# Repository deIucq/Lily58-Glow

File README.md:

# Lily58 - χ
ビルドガイドは[こちら](https://github.com/deIucq/Lily58-X/blob/master/buildguide.md)

BuildGuide is [here](https://github.com/deIucq/Lily58-X/blob/master/buildguide.md)

Lily58-χ(カイ)はLily58からforkされた[Lily58-glow](https://github.com/qtkb/Lily58-Glow)に以下の変更を加えたものです。
検索性向上のために，ここ以外ではLily58-Xと表記します。

- RGBLEDのpad配置をSK6812mini-e用に変更
- Underglow用LEDの場所・数を変更
- BLE Micro Proのインジケータ用にLEDを追加
- トラックパッド用のピンヘッダ・ネジ穴を追加
- 縁を覆うようなケースを追加
- I2Cと単線シリアルをスイッチできるようにジャンパーを追加
- TRRSジャックのピンアサインを変更(moduloと同様のピンアサイン)

Lily58-χ(chi) is a forked version of [Lily58-glow](https://github.com/qtkb/Lily58-Glow) from Lily58 with the following changes.

- Change RGB LED pad to SK6812mini-e's one.
- Change place and number of LEDs for underglow.
- Add LED for BLE Micro Pro's indicator.
- Add new Pinheader for trackpad modules.
- Add case that can cover edge.
- Add jumber for switching I2C and Serial
- Change TRRS pin assign

このプロジェクトは開発中です。PCBの設計にミスがある可能性があります。
This project is still in progress. There may be some mistakes in PCB design.

# Parts

| Part Name                                                    | Quantity |
| ------------------------------------------------------------ | -------- |
| PCB                                                          | 2        |
| Top Case,Mid Case,Bottom Case(t2 acrylic)                    | 2        |
| Pro Micro or BLE Micro Pro                                   | 2        |
| Choc Key Switch                                              | 58       |
| Keycap                                                       | 58       |
| SK6812-MINI-E                                                | 58       |
| OLED                                                         | 2        |
| Diode 1N4148W                                                | 58       |
| Tact switch                                                  | 2        |
| TRRS jack (option for Pro Micro)                             | 2        |
| TRRS cable (opton for Pro Micro)                             | 1        |
| M2 screw 10mm                                                | 10       |
| M2 Nut                                                       | 20       |
| M2 spacer 10mm                                               | 4        |
| M2 screw 4mm                                                 | 8        |
| Urethane cushion                                             | 10       |
| Low profile pin header(1×4 & 1×6)                            | 2        |
| [option] RKJXY1000006 trackpad with DIP convertPCB           | 1        |
| [option] 1608 LED                                            | 1        |
| [option] Constant current diode or resistor                  | 1        |

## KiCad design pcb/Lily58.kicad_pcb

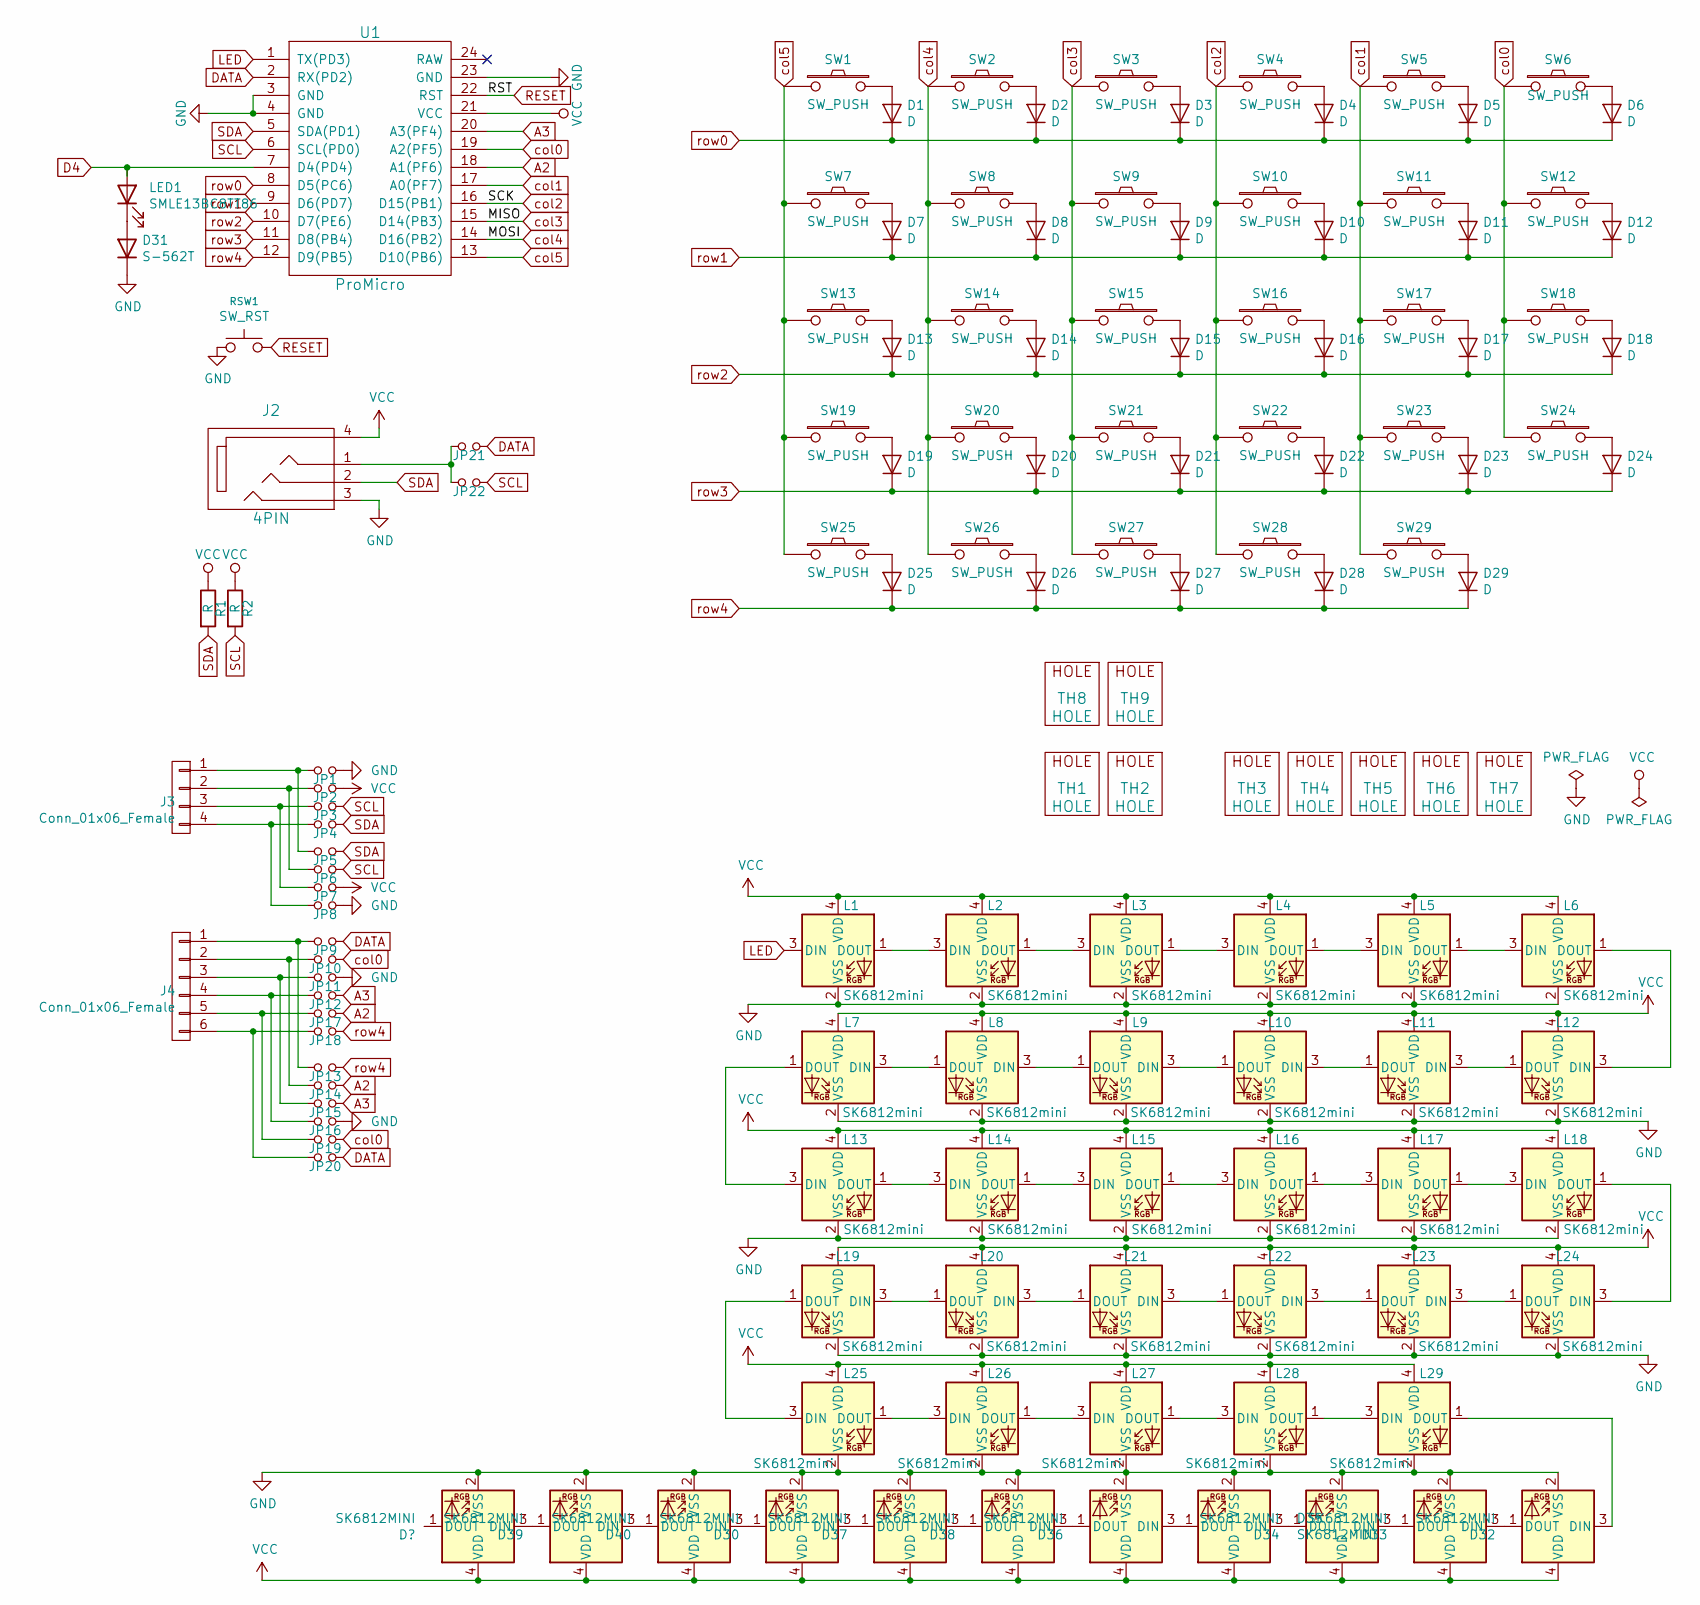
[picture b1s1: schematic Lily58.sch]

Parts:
D1, D2, D3, D4, D5, D6, D7, D8, D9, D10, D11, D12, D13, D14, D15, D16, D17, D18, D19, D20, D21, D22, D23, D24, D25, D26, D27, D28, D29: D; Diode_SOD123
D30, D32, D33, D34, D35, D36, D37, D38, D39, D40: SK6812MINI; SK6812MINI_underglow_rev
D31: S-562T; D_1206_3216Metric_Pad1.42x1.75mm_HandSolder
J2: 4PIN; MJ-4PP-9
J3: Conn_01x06_Female; OLED_4Pin
J4: Conn_01x06_Female; OLED_6Pin
JP1, JP2, JP3, JP4, JP5, JP6, JP7, JP8, JP9, JP10, JP11, JP12, JP13, JP14, JP15, JP16, JP17, JP18, JP19, JP20: Jumper_NO_Small; Jumper
JP21: 1S; Jumper
JP22: I2C; Jumper
L1, L2, L3, L4, L5, L6, L7, L8, L9, L10, L11, L12, L13, L14, L15, L16, L17, L18, L19, L20, L21, L22, L23, L24, L25, L26, L27, L28, L29: SK6812mini; SK6812MINI_rev
LED1: SMLE13BC8TT86; LED_0603_1608Metric_Pad1.05x0.95mm_HandSolder
R1, R2: R; RESISTOR_mini
RSW1: SW_RST; TACT_SWITCH_TVBP06
SW1, SW2, SW3, SW4, SW5, SW6, SW7, SW8, SW9, SW10, SW11, SW12, SW13, SW14, SW15, SW16, SW17, SW18, SW19, SW20, SW21, SW22, SW23, SW24, SW25, SW27, SW28, SW29: SW_PUSH; MX_PG1350_FLIP_HOLES_18mm
SW26: SW_PUSH; MX_PG1350_FLIP_HOLES_27mm
TH1, TH2, TH8, TH9: HOLE; HOLE_M2
TH3, TH4, TH5, TH6, TH7: HOLE; HOLE_M2_TH
U1: ProMicro; ProMicro_rev2

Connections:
A2: JP14.2, JP17.2, U1.18 (A1(PF6))
A3: JP12.2, JP15.2, U1.20 (A3(PF4))
D4: LED1.2 (A), U1.7 (D4(PD4))
DATA: JP9.2, JP20.2, JP21.2, U1.2 (RX(PD2))
GND: D30.2 (VSS), D31.1 (K), D32.2 (VSS), D33.2 (VSS), D34.2 (VSS), D35.2 (VSS), D36.2 (VSS), D37.2 (VSS), D38.2 (VSS), D39.2 (VSS), D40.2 (VSS), J2.3, JP1.2, JP8.2, JP11.2, JP16.2, L1.2 (VSS), L2.2 (VSS), L3.2 (VSS), L4.2 (VSS), L5.2 (VSS), L6.2 (VSS), L7.2 (VSS), L8.2 (VSS), L9.2 (VSS), L10.2 (VSS), L11.2 (VSS), L12.2 (VSS), L13.2 (VSS), L14.2 (VSS), L15.2 (VSS), L16.2 (VSS), L17.2 (VSS), L18.2 (VSS), L19.2 (VSS), L20.2 (VSS), L21.2 (VSS), L22.2 (VSS), L23.2 (VSS), L24.2 (VSS), L25.2 (VSS), L26.2 (VSS), L27.2 (VSS), L28.2 (VSS), L29.2 (VSS), RSW1.1, U1.3 (GND), U1.4 (GND), U1.23 (GND); also elsewhere on the board
LED: L1.3 (DIN), U1.1 (TX(PD3))
unnamed: D1.2 (A), SW1.2
unnamed: D2.2 (A), SW2.2
unnamed: D3.2 (A), SW3.2
unnamed: D4.2 (A), SW4.2
unnamed: D5.2 (A), SW5.2
unnamed: D6.2 (A), SW6.2
unnamed: D7.2 (A), SW7.2
unnamed: D8.2 (A), SW8.2
unnamed: D9.2 (A), SW9.2
unnamed: D10.2 (A), SW10.2
unnamed: D11.2 (A), SW11.2
unnamed: D12.2 (A), SW12.2
unnamed: D13.2 (A), SW13.2
unnamed: D14.2 (A), SW14.2
unnamed: D15.2 (A), SW15.2
unnamed: D16.2 (A), SW16.2
unnamed: D17.2 (A), SW17.2
unnamed: D18.2 (A), SW18.2
unnamed: D19.2 (A), SW19.2
unnamed: D20.2 (A), SW20.2
unnamed: D21.2 (A), SW21.2
unnamed: D22.2 (A), SW22.2
unnamed: D23.2 (A), SW23.2
unnamed: D24.2 (A), SW24.2
unnamed: D25.2 (A), SW25.2
unnamed: D26.2 (A), SW26.2
unnamed: D27.2 (A), SW27.2
unnamed: D28.2 (A), SW28.2
unnamed: D29.2 (A), SW29.2
unnamed: D30.1 (DOUT), D40.3 (DIN)
unnamed: D30.3 (DIN), D37.1 (DOUT)
unnamed: D31.2 (A), LED1.1 (K)
unnamed: D32.1 (DOUT), D33.3 (DIN)
unnamed: D32.3 (DIN), L29.1 (DOUT)
unnamed: D33.1 (DOUT), D34.3 (DIN)
unnamed: D34.1 (DOUT), D35.3 (DIN)
unnamed: D35.1 (DOUT), D36.3 (DIN)
unnamed: D36.1 (DOUT), D38.3 (DIN)
unnamed: D37.3 (DIN), D38.1 (DOUT)
unnamed 45: D39.1 (DOUT); also elsewhere on the board
unnamed: D39.3 (DIN), D40.1 (DOUT)
unnamed: J2.1, JP21.1, JP22.1
unnamed: J3.1, JP1.1, JP5.1
unnamed: J3.2, JP2.1, JP6.1
unnamed: J3.3, JP3.1, JP7.1
unnamed: J3.4, JP4.1, JP8.1
unnamed: J4.1, JP9.1, JP13.1
unnamed: J4.2, JP10.1, JP14.1
unnamed: J4.3, JP11.1, JP15.1
unnamed: J4.4, JP12.1, JP16.1
unnamed: J4.5, JP17.1, JP19.1
unnamed: J4.6, JP18.1, JP20.1
unnamed: L1.1 (DOUT), L2.3 (DIN)
unnamed: L2.1 (DOUT), L3.3 (DIN)
unnamed: L3.1 (DOUT), L4.3 (DIN)
unnamed: L4.1 (DOUT), L5.3 (DIN)
unnamed: L5.1 (DOUT), L6.3 (DIN)
unnamed: L7.3 (DIN), L8.1 (DOUT)
unnamed: L8.3 (DIN), L9.1 (DOUT)
unnamed: L9.3 (DIN), L10.1 (DOUT)
unnamed: L10.3 (DIN), L11.1 (DOUT)
unnamed: L11.3 (DIN), L12.1 (DOUT)
unnamed: L6.1 (DOUT), L12.3 (DIN)
unnamed: L13.1 (DOUT), L14.3 (DIN)
unnamed: L7.1 (DOUT), L13.3 (DIN)
unnamed: L14.1 (DOUT), L15.3 (DIN)
unnamed: L15.1 (DOUT), L16.3 (DIN)
unnamed: L16.1 (DOUT), L17.3 (DIN)
unnamed: L17.1 (DOUT), L18.3 (DIN)
unnamed: L18.1 (DOUT), L24.3 (DIN)
unnamed: L19.1 (DOUT), L25.3 (DIN)
unnamed: L19.3 (DIN), L20.1 (DOUT)
unnamed: L20.3 (DIN), L21.1 (DOUT)
unnamed: L21.3 (DIN), L22.1 (DOUT)
unnamed: L22.3 (DIN), L23.1 (DOUT)
unnamed: L23.3 (DIN), L24.1 (DOUT)
unnamed: L25.1 (DOUT), L26.3 (DIN)
unnamed: L26.1 (DOUT), L27.3 (DIN)
unnamed: L27.1 (DOUT), L28.3 (DIN)
unnamed: L28.1 (DOUT), L29.3 (DIN)
RESET: RSW1.2, U1.22 (RST)
SCL: JP3.2, JP6.2, JP22.2, R2.2, U1.6 (SCL(PD0))
SDA: J2.2, JP4.2, JP5.2, R1.2, U1.5 (SDA(PD1))
VCC: D30.4 (VDD), D32.4 (VDD), D33.4 (VDD), D34.4 (VDD), D35.4 (VDD), D36.4 (VDD), D37.4 (VDD), D38.4 (VDD), D39.4 (VDD), D40.4 (VDD), J2.4, JP2.2, JP7.2, L1.4 (VDD), L2.4 (VDD), L3.4 (VDD), L4.4 (VDD), L5.4 (VDD), L6.4 (VDD), L7.4 (VDD), L8.4 (VDD), L9.4 (VDD), L10.4 (VDD), L11.4 (VDD), L12.4 (VDD), L13.4 (VDD), L14.4 (VDD), L15.4 (VDD), L16.4 (VDD), L17.4 (VDD), L18.4 (VDD), L19.4 (VDD), L20.4 (VDD), L21.4 (VDD), L22.4 (VDD), L23.4 (VDD), L24.4 (VDD), L25.4 (VDD), L26.4 (VDD), L27.4 (VDD), L28.4 (VDD), L29.4 (VDD), R1.1, R2.1, U1.21 (VCC); also elsewhere on the board
col0: JP10.2, JP19.2, SW6.1, SW12.1, SW18.1, SW24.1, U1.19 (A2(PF5))
col1: SW5.1, SW11.1, SW17.1, SW23.1, SW29.1, U1.17 (A0(PF7))
col2: SW4.1, SW10.1, SW16.1, SW22.1, SW28.1, U1.16 (D15(PB1))
col3: SW3.1, SW9.1, SW15.1, SW21.1, SW27.1, U1.15 (D14(PB3))
col4: SW2.1, SW8.1, SW14.1, SW20.1, SW26.1, U1.14 (D16(PB2))
col5: SW1.1, SW7.1, SW13.1, SW19.1, SW25.1, U1.13 (D10(PB6))
row0: D1.1 (K), D2.1 (K), D3.1 (K), D4.1 (K), D5.1 (K), D6.1 (K), U1.8 (D5(PC6))
row1: D7.1 (K), D8.1 (K), D9.1 (K), D10.1 (K), D11.1 (K), D12.1 (K), U1.9 (D6(PD7))
row2: D13.1 (K), D14.1 (K), D15.1 (K), D16.1 (K), D17.1 (K), D18.1 (K), U1.10 (D7(PE6))
row3: D19.1 (K), D20.1 (K), D21.1 (K), D22.1 (K), D23.1 (K), D24.1 (K), U1.11 (D8(PB4))
row4: D25.1 (K), D26.1 (K), D27.1 (K), D28.1 (K), D29.1 (K), JP13.2, JP18.2, U1.12 (D9(PB5))

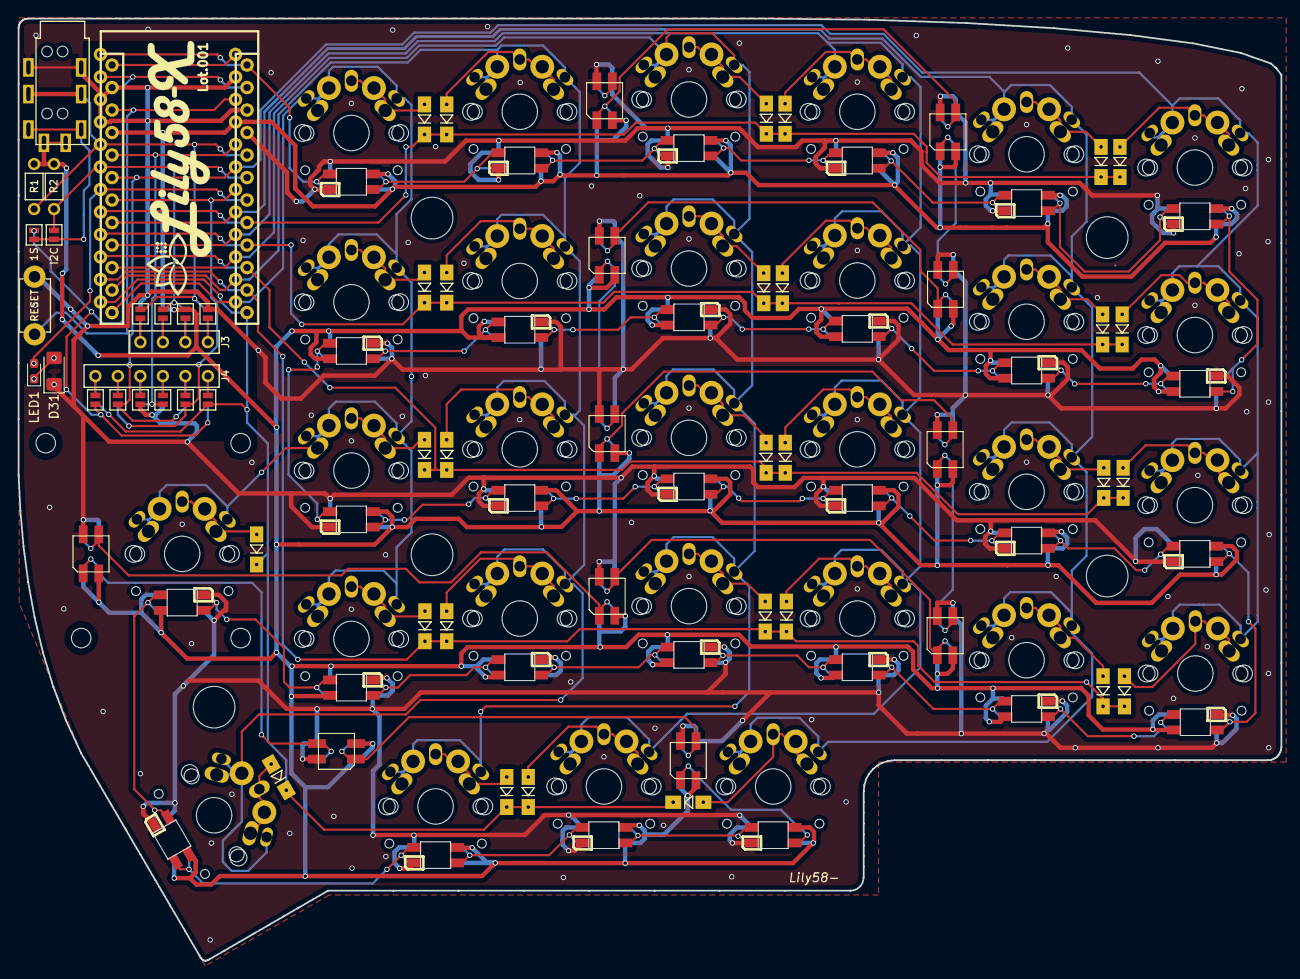
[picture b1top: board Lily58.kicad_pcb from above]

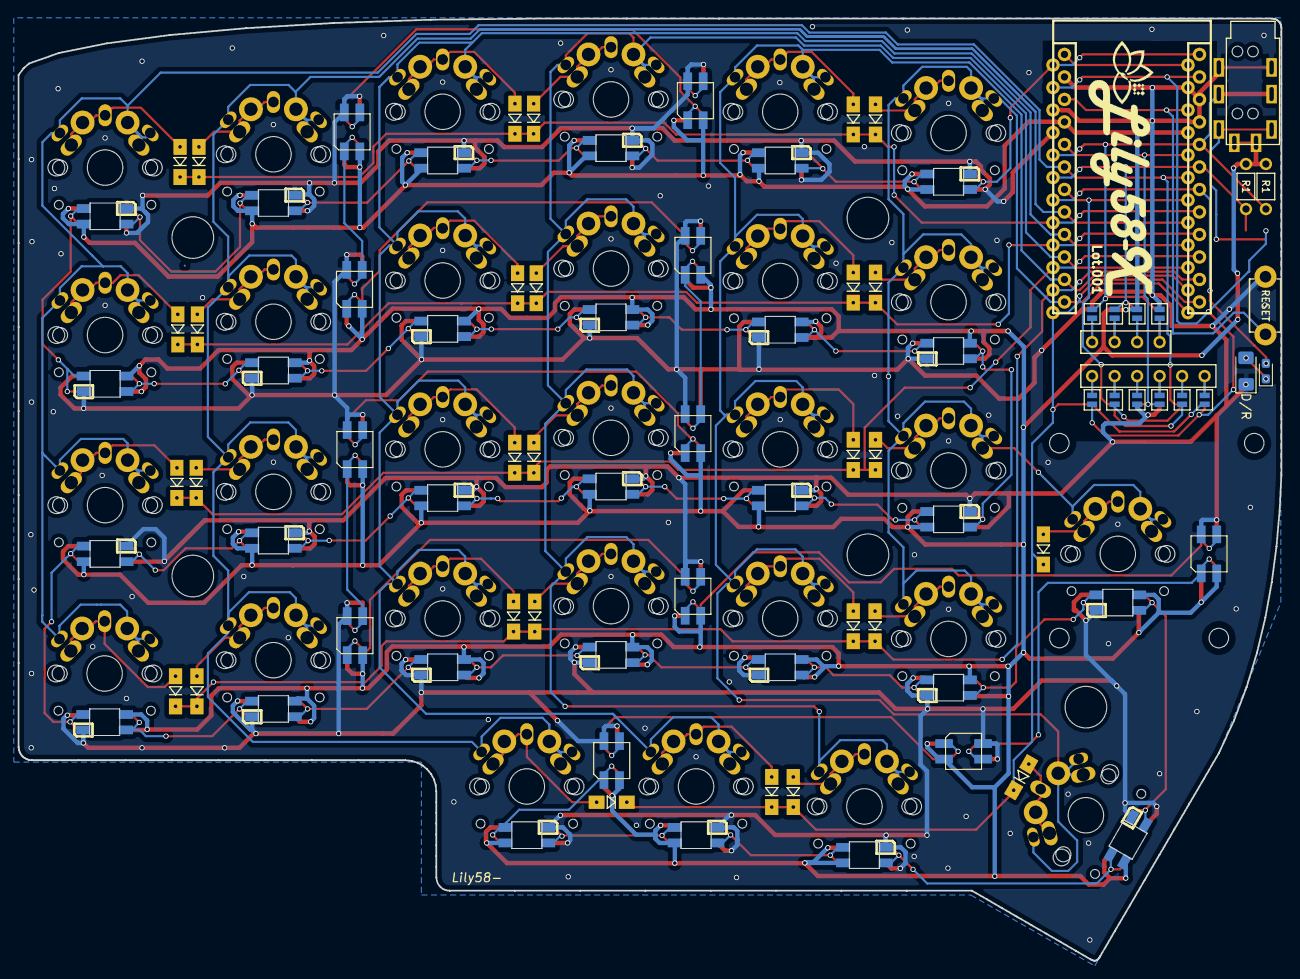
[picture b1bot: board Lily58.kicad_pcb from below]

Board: 2 copper layers, 142.5 x 106.3 mm, 138 parts (38 on the bottom side), 101 nets.

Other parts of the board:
D41: SK6812MINI; SK6812MINI_underglow_rev

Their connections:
GND: D41.2; also elsewhere on the board
unnamed 45: D41.3; also elsewhere on the board
VCC: D41.4; also elsewhere on the board

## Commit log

2021-11-14 add LED for BLE Micro Pro indicator
2021-11-14 change partlist
2021-11-14 add diode and LED footprint for lily58
2021-11-14 changed oled footprint(4pin -> 6pin)
2021-11-14 change pinsocket 4pin -> 6pin
2021-11-15 add pcb pic
2021-11-15 changed LED pad for SK6812MINI-E
2021-11-15 copy lily58 case
2021-11-15 fix typo
2021-11-15 change pad and delete underglow
2021-11-16 add pinheader and logo
2021-11-16 add via
2021-11-16 update LICENSE
2021-11-17 brush up PCB
2021-11-17 add gerber
2021-11-17 add large case
2021-11-20 update pcb pic
2021-11-20 udpate case
2021-11-28 change silk
2021-12-01 change case
2021-12-02 add sk6812mini
2021-12-02 update sk6812mini pin assgin
2021-12-02 change 3.5mm jack assign
2021-12-05 Revert "change 3.5mm jack assign"
    This reverts commit aa684eaece7f45b972ff72976500a763c7363c79.
2021-12-10 change pcb - delete underglow - change pins - change holes for sk6812mini-e
2021-12-10 add buildguide
2021-12-10 change gerber place
2021-12-10 add via hex
2021-12-10 add .gitignore desktop.ini
2021-12-10 config gerbers
2021-12-10 update pcb
2021-12-12 update buildguide
2021-12-12 add SMD only diode
2021-12-12 add underglow
2021-12-13 add default json for BMP
2021-12-13 change directory
2021-12-13 add 001 gerber
2021-12-14 fix joystick pinout
2021-12-15 refuctor pcb
